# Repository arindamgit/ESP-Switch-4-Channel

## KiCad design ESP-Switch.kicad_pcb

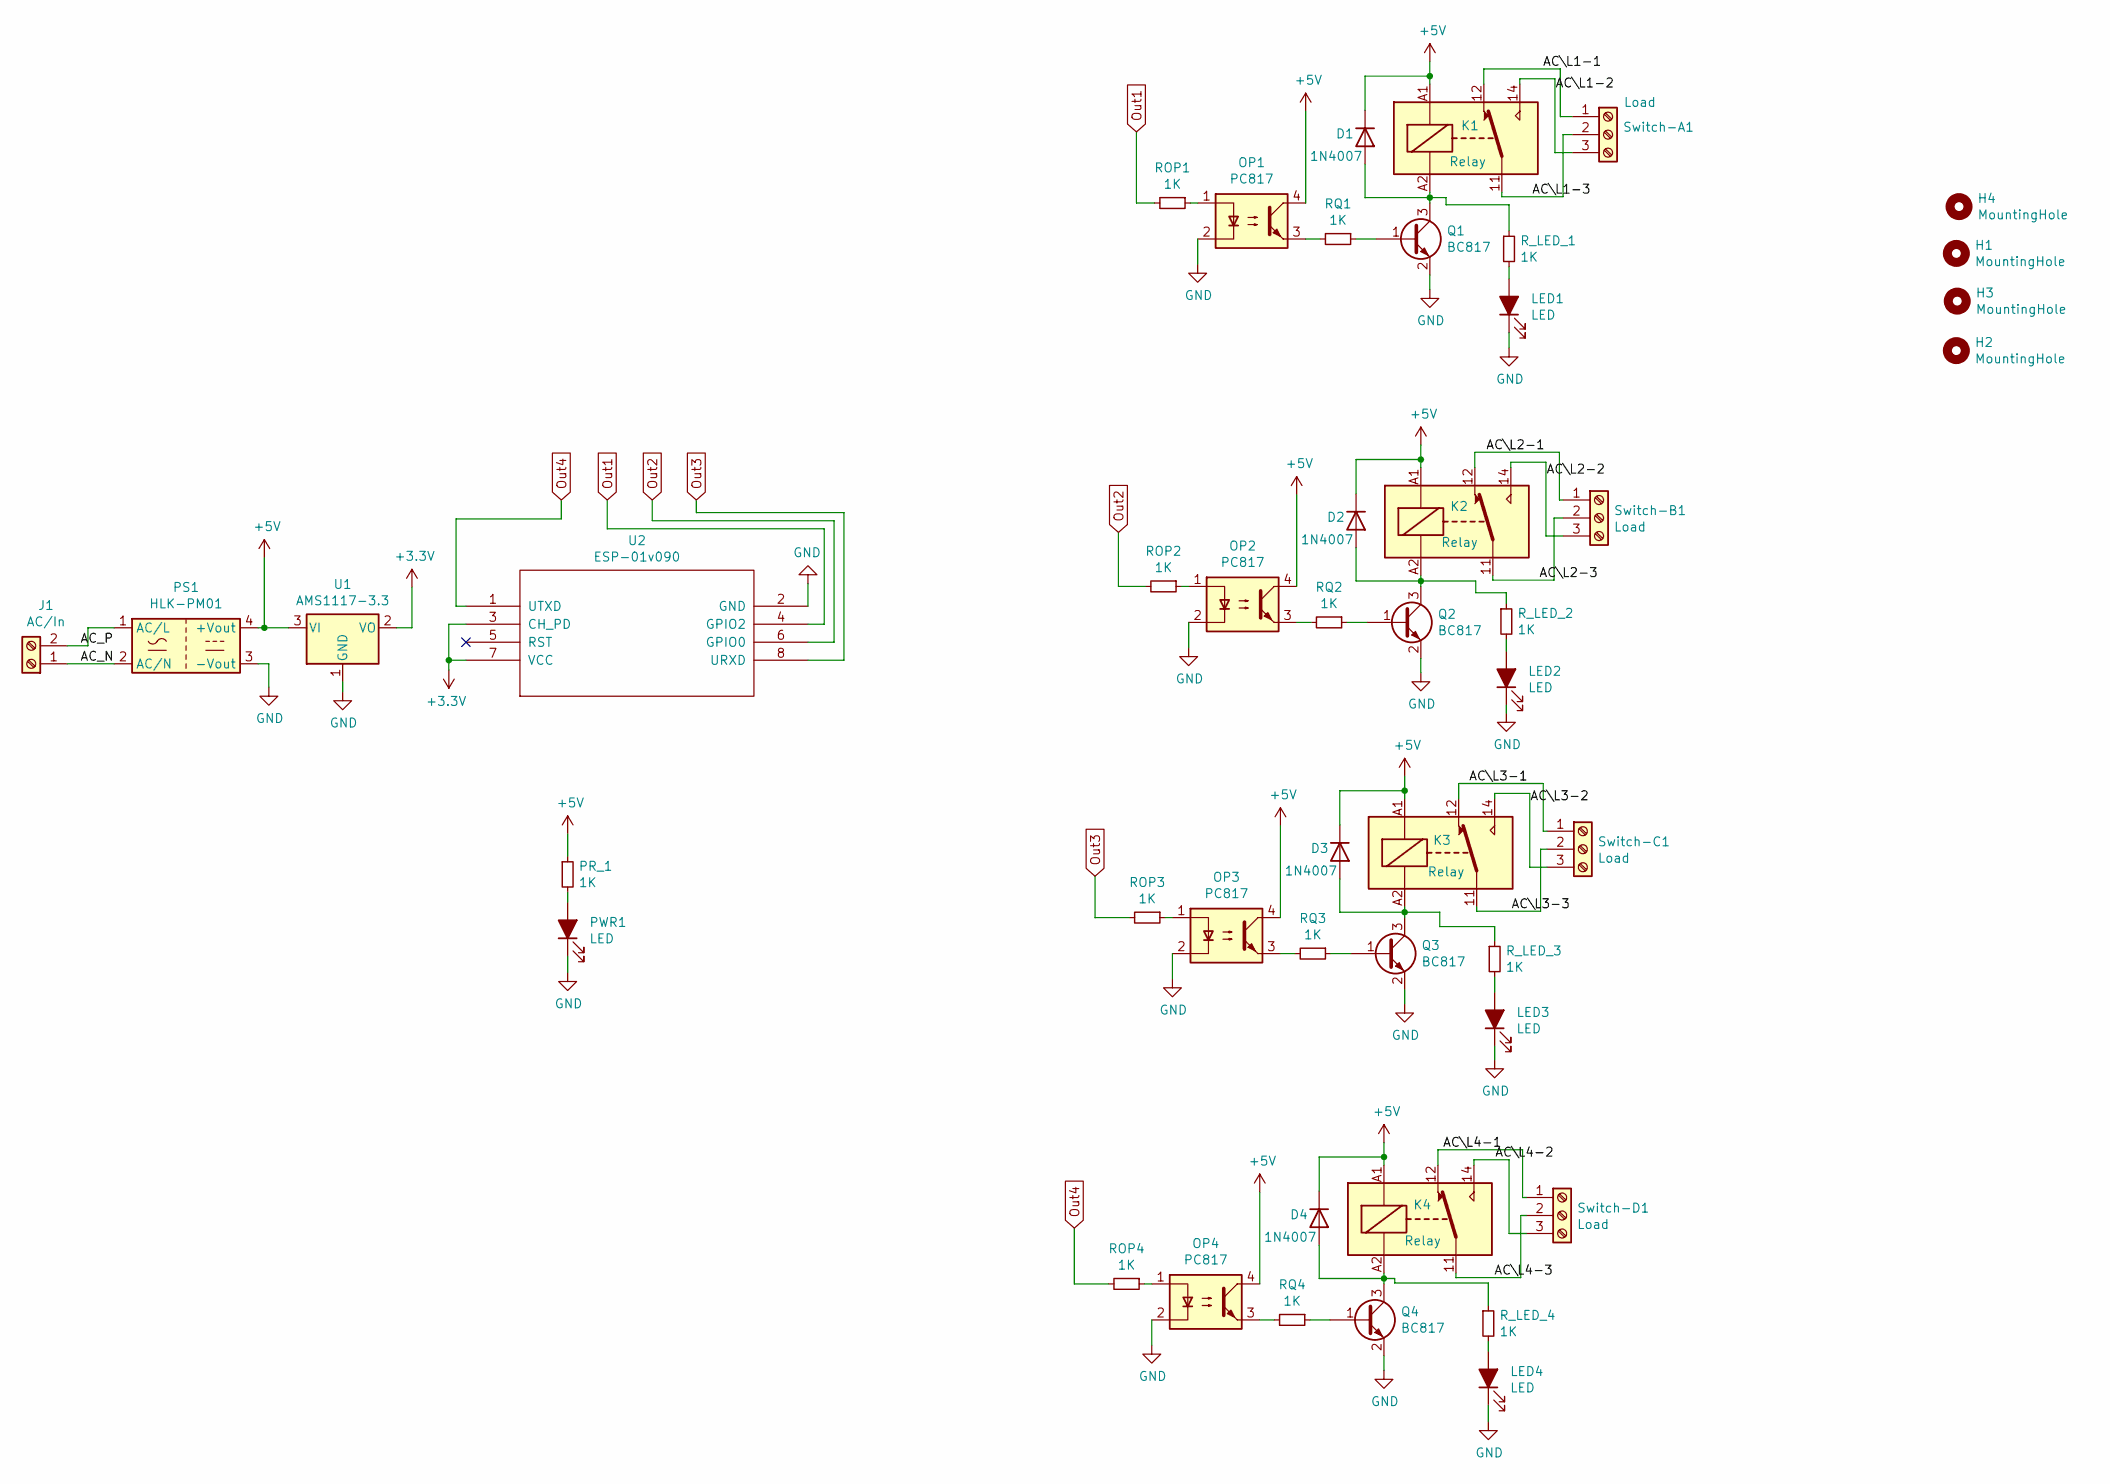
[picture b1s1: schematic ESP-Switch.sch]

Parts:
D1, D2, D3, D4: 1N4007; D_SMA_Handsoldering
H1, H2, H3, H4: MountingHole; MountingHole_3.2mm_M3_DIN965
J1: AC/In; TerminalBlock_Altech_AK300-2_P5.00mm
K1, K2, K3, K4: Relay; Relay_SPDT_Finder_36.11
LED1, LED2, LED3, LED4: LED; LED_0805_2012Metric
OP1, OP2, OP3, OP4: PC817; DIP-4_W7.62mm
PR_1: 1K; R_0805_2012Metric
PS1: HLK-PM01; Converter_ACDC_HiLink_HLK-PMxx
PWR1: LED; LED_0805_2012Metric
Q1, Q2, Q3, Q4: BC817; SOT-23
ROP1, ROP2, ROP3, ROP4: 1K; R_0805_2012Metric
RQ1, RQ2, RQ3, RQ4: 1K; R_0805_2012Metric
R_LED_1, R_LED_2, R_LED_3, R_LED_4: 1K; R_0805_2012Metric
Switch-A1: Load; TerminalBlock_Altech_AK300-3_P5.00mm
Switch-B1: Load; TerminalBlock_Altech_AK300-3_P5.00mm
Switch-C1: Load; TerminalBlock_Altech_AK300-3_P5.00mm
Switch-D1: Load; TerminalBlock_Altech_AK300-3_P5.00mm
U1: AMS1117-3.3; SOT-223-3_TabPin2
U2: ESP-01v090; ESP-01

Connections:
+3V3: U1.2 (VO), U2.3 (CH_PD), U2.7 (VCC)
+5V: D1.1 (K), D2.1 (K), D3.1 (K), D4.1 (K), K1.A1, K2.A1, K3.A1, K4.A1, OP1.4, OP2.4, OP3.4, OP4.4, PR_1.1, PS1.4 (+Vout), U1.3 (VI)
/AC\L1-1: K1.12, Switch-A1.1
/AC\L1-2: K1.14, Switch-A1.3
/AC\L1-3: K1.11, Switch-A1.2
/AC\L2-1: K2.12, Switch-B1.1
/AC\L2-2: K2.14, Switch-B1.3
/AC\L2-3: K2.11, Switch-B1.2
/AC\L3-1: K3.12, Switch-C1.1
/AC\L3-2: K3.14, Switch-C1.3
/AC\L3-3: K3.11, Switch-C1.2
/AC\L4-1: K4.12, Switch-D1.1
/AC\L4-2: K4.14, Switch-D1.3
/AC\L4-3: K4.11, Switch-D1.2
/AC_N: J1.1, PS1.2 (AC/N)
/AC_P: J1.2, PS1.1 (AC/L)
GND: LED1.1 (K), LED2.1 (K), LED3.1 (K), LED4.1 (K), OP1.2, OP2.2, OP3.2, OP4.2, PS1.3 (-Vout), PWR1.1 (K), Q1.2 (E), Q2.2 (E), Q3.2 (E), Q4.2 (E), U1.1 (GND), U2.2 (GND)
unnamed: D1.2 (A), K1.A2, Q1.3 (C), R_LED_1.1
unnamed: D2.2 (A), K2.A2, Q2.3 (C), R_LED_2.1
unnamed: D3.2 (A), K3.A2, Q3.3 (C), R_LED_3.1
unnamed: D4.2 (A), K4.A2, Q4.3 (C), R_LED_4.1
unnamed: LED1.2 (A), R_LED_1.2
unnamed: LED2.2 (A), R_LED_2.2
unnamed: LED3.2 (A), R_LED_3.2
unnamed: LED4.2 (A), R_LED_4.2
unnamed: OP1.1, ROP1.1
unnamed: OP1.3, RQ1.2
unnamed: OP2.1, ROP2.1
unnamed: OP2.3, RQ2.2
unnamed: OP3.1, ROP3.1
unnamed: OP3.3, RQ3.2
unnamed: OP4.1, ROP4.1
unnamed: OP4.3, RQ4.2
unnamed: PR_1.2, PWR1.2 (A)
unnamed: Q1.1 (B), RQ1.1
unnamed: Q2.1 (B), RQ2.1
unnamed: Q3.1 (B), RQ3.1
unnamed: Q4.1 (B), RQ4.1
Out1: ROP1.2, U2.4 (GPIO2)
Out2: ROP2.2, U2.6 (GPIO0)
Out3: ROP3.2, U2.8 (URXD)
Out4: ROP4.2, U2.1 (UTXD)

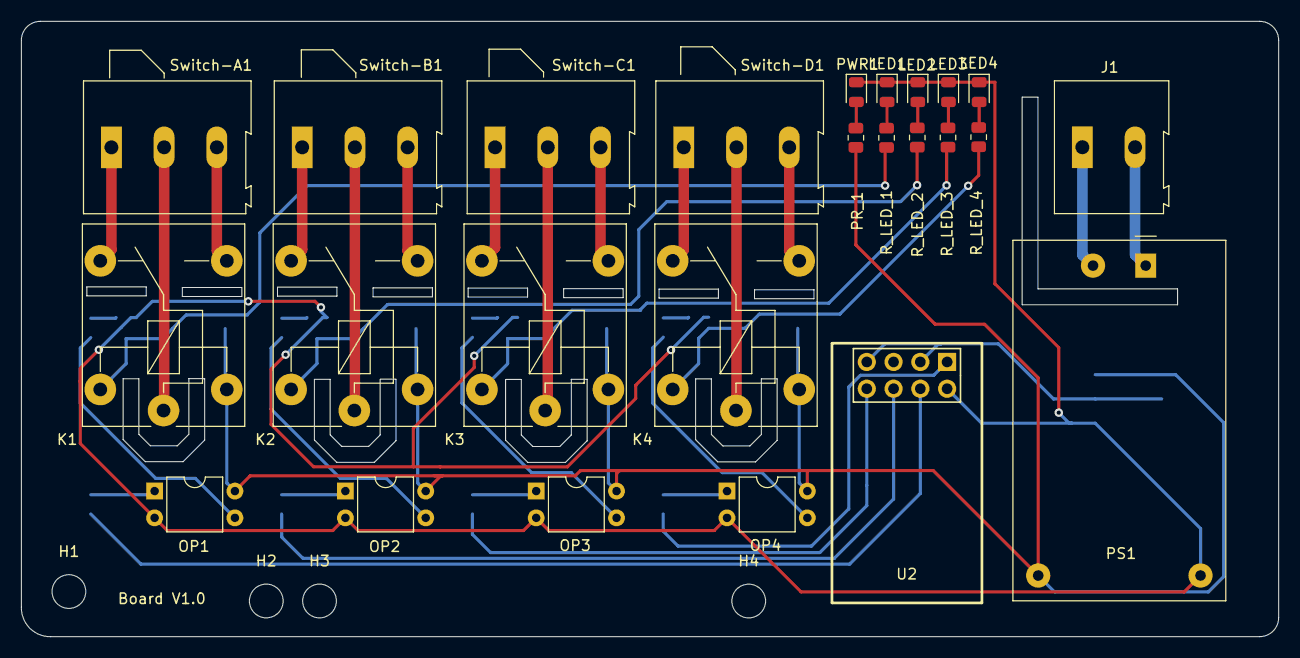
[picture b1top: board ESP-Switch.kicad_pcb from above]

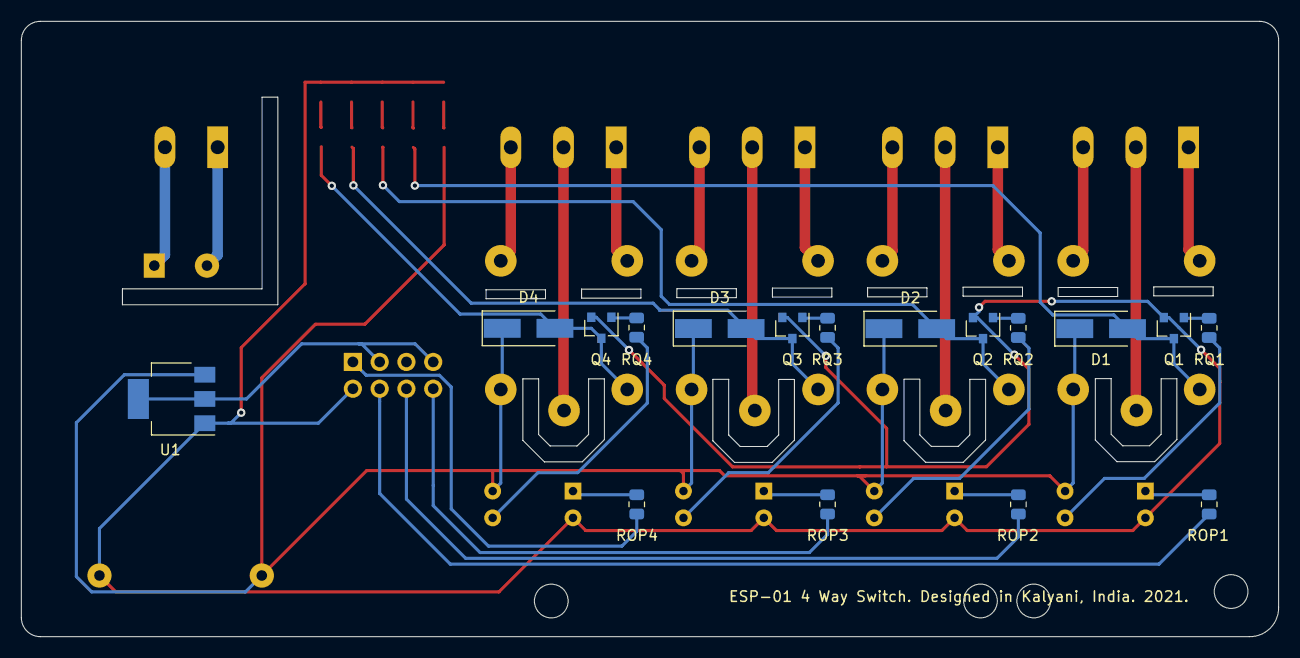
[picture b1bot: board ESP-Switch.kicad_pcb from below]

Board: 2 copper layers, 119.3 x 58.4 mm, 46 parts (17 on the bottom side), 42 nets.

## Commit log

2021-10-12 relay version
2021-10-13 dimmer version
2021-10-31 First commit - on/off endpoint works
2021-11-06 firware
2021-11-06 fixing the problems
